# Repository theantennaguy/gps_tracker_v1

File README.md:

# gps_tracker_v1
 
This project is discontinued. I'm working on a new version, but so far it's only in the design phase.

The hardware project for this project is complete and functional. A board-bring-up was sucessfully performed and all is operational. The code was never completed, only basic functions for capturing GPS coordinates and sending SMSs, but I never got ot finish a working application for it.

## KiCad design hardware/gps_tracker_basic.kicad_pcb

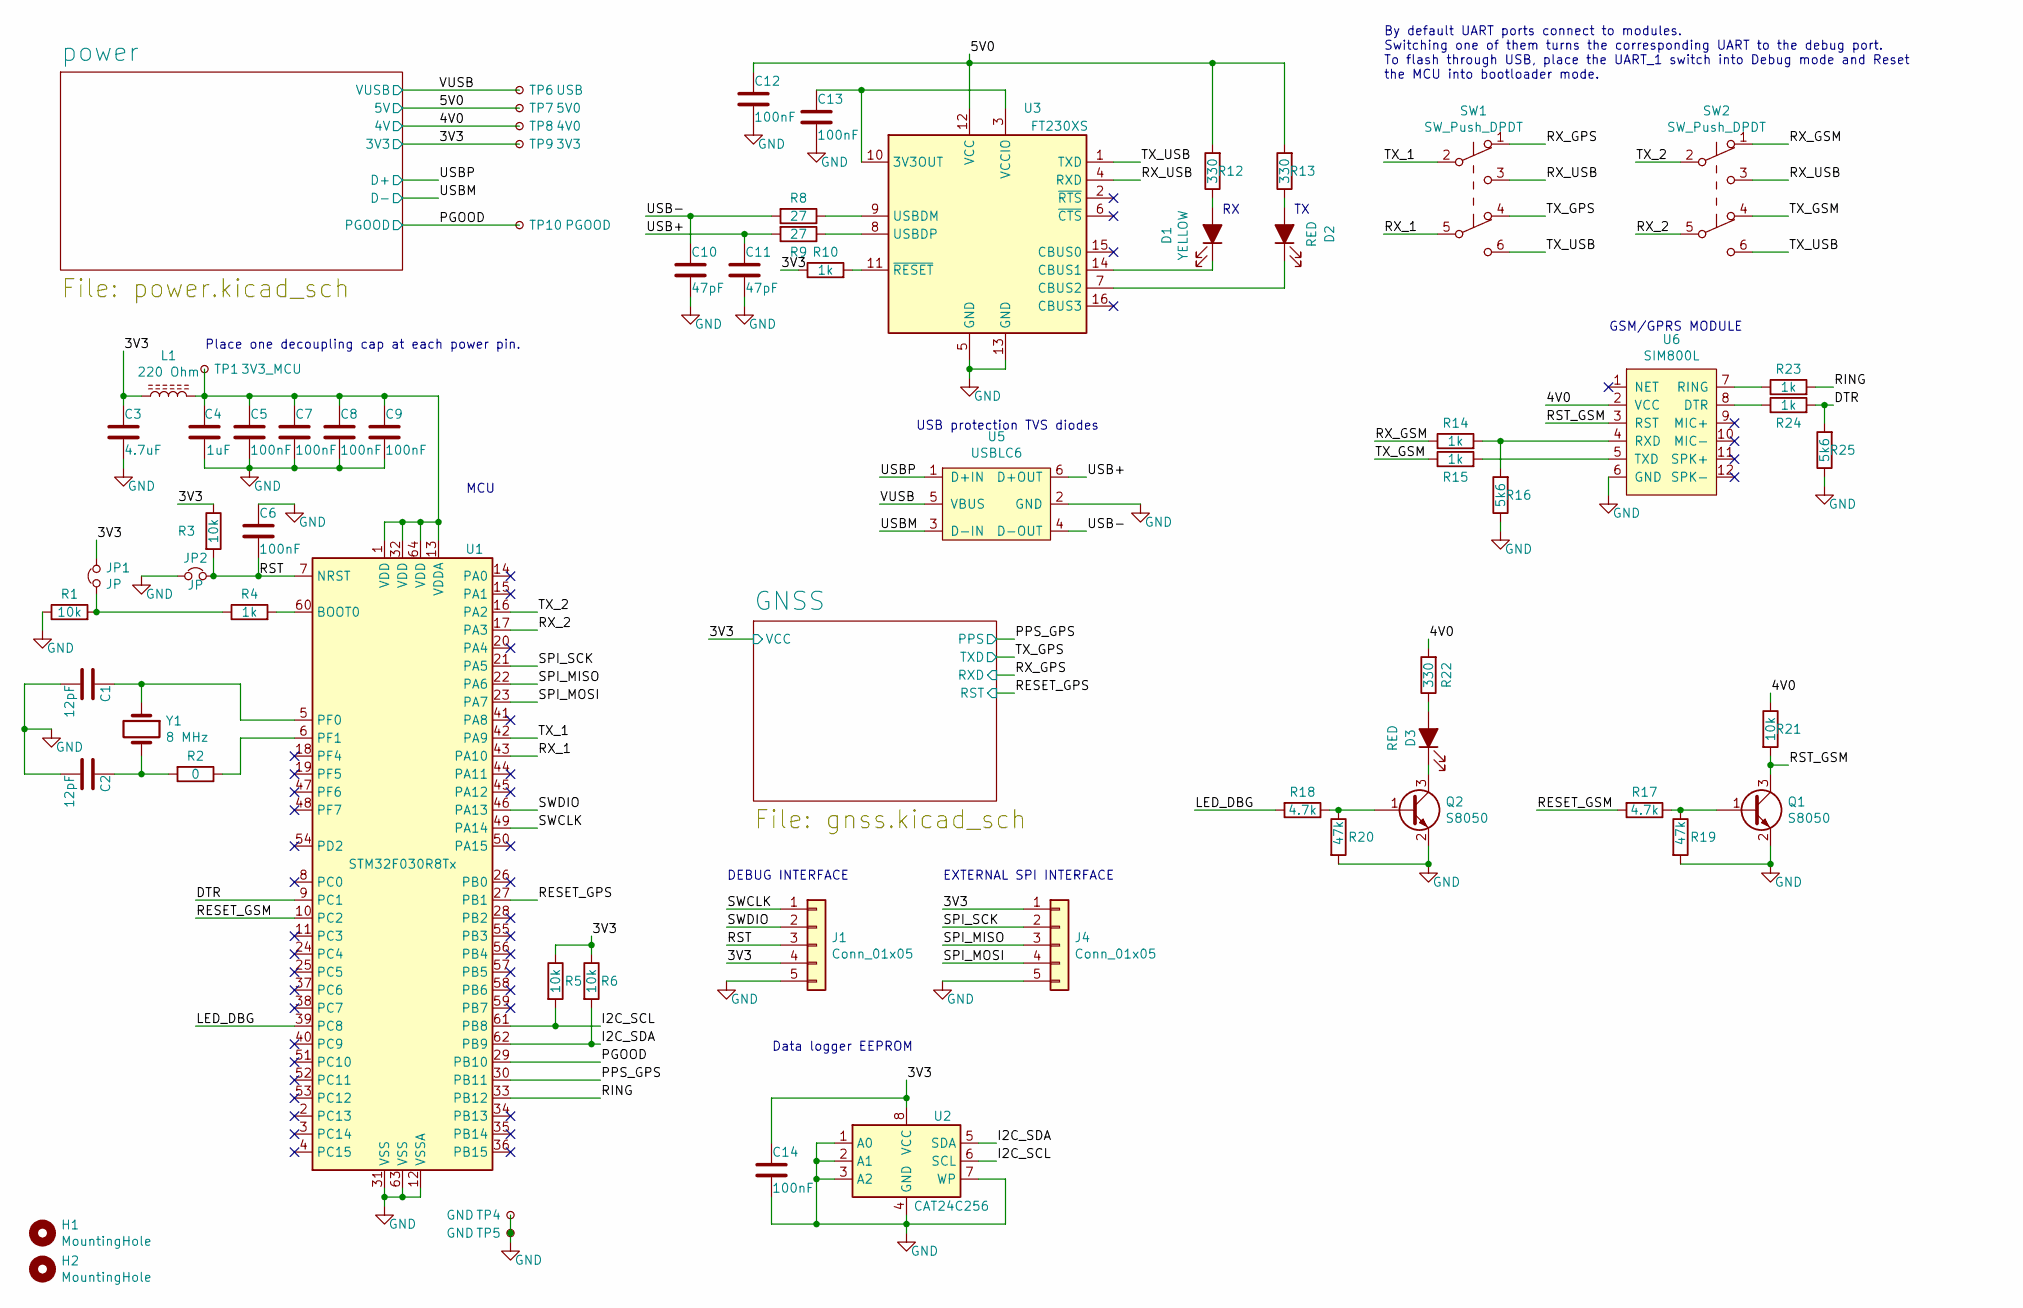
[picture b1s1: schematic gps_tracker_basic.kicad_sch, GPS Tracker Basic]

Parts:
C1, C2: 12pF; C_0402_1005Metric; Mfr. PN 0402CG120J500NT; LCSC C1547
C3: 4.7uF; C_0603_1608Metric; Mfr. PN CL10A475KO8NNNC; LCSC C19666
C4: 1uF; C_0603_1608Metric; Mfr. PN CL10A105KB8NNNC; LCSC C15849
C5, C6, C7, C8, C9, C12, C13, C14: 100nF; C_0402_1005Metric; Mfr. PN CL05B104KO5NNNC; LCSC C1525
C10, C11: 47pF; C_0402_1005Metric; Mfr. PN 0402CG470J500NT; LCSC C1567
D1: YELLOW; LED_0805_2012Metric; Mfr. PN 17-21SUYC/TR8; LCSC C2296
D2, D3: RED; LED_0805_2012Metric; Mfr. PN FC-2012HRK-620D; LCSC C84256
H1, H2: MountingHole; MountingHole_2.5mm
J1, J4: Conn_01x05; PinHeader_1x05_P2.54mm_Horizontal
JP1, JP2: JP; SolderJumper-2_P1.3mm_Open_RoundedPad1.0x1.5mm
L1: 220 Ohm; L_0603_1608Metric; Mfr. PN BLM18BB221SN1D; LCSC C85826
Q1, Q2: S8050; SOT-23; Mfr. PN S8050; LCSC C2146
R1, R3, R5, R6, R21: 10k; R_0402_1005Metric; Mfr. PN 0402WGF1002TCE; LCSC C25744
R2: 0; R_0603_1608Metric
R4, R10, R14, R15, R23, R24: 1k; R_0402_1005Metric; Mfr. PN 0402WGF1001TCE; LCSC C11702
R8, R9: 27; R_0402_1005Metric; Mfr. PN RT0402FRE0727RL
R12, R13, R22: 330; R_0402_1005Metric; Mfr. PN 0402WGF3300TCE; LCSC C25104
R16, R25: 5k6; R_0402_1005Metric; Mfr. PN 0402WGF5601TCE; LCSC C25908
R17, R18: 4.7k; R_0402_1005Metric; Mfr. PN 0402WGF4701TCE; LCSC C25900
R19, R20: 47k; R_0402_1005Metric; Mfr. PN 0402WGF4702TCE; LCSC C25792
SW1, SW2: SW_Push_DPDT; SW_CuK_JS202011CQN_DPDT_Straight; Mfr. PN JS202011JCQN
TP1: 3V3_MCU; TestPoint_Pad_D1.5mm
TP4, TP5: GND; TestPoint_Pad_D1.5mm
TP6: USB; TestPoint_Pad_D1.5mm
TP7: 5V0; TestPoint_Pad_D1.5mm
TP8: 4V0; TestPoint_Pad_D1.5mm
TP9: 3V3; TestPoint_Pad_D1.5mm
TP10: PGOOD; TestPoint_Pad_D1.5mm
U1: STM32F030R8Tx; LQFP-64_10x10mm_P0.5mm; Mfr. PN STM32F030R8T6; LCSC C39105
U2: CAT24C256; SOIC-8_3.9x4.9mm_P1.27mm; Mfr. PN AT24C256C-SSHL-T; LCSC C6482
U3: FT230XS; SSOP-16_3.9x4.9mm_P0.635mm; Mfr. PN FT230XS
U5: USBLC6; SOT-23-6; Mfr. PN USBLC6-2SC6; LCSC C7519
U6: SIM800L; SIM_800L_breakout; Mfr. PN SIM800L
Y1: 8 MHz; Crystal_SMD_5032-2Pin_5.0x3.2mm; Mfr. PN ECS-80-12-30Q-DS-TR

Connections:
/3V3: C3.1, C14.1, J1.4, J4.1, JP1.2, L1.1, R3.1, R5.1, R6.1, R10.1, TP9.1, U2.8 (VCC); also elsewhere on the board
/4V0: R21.1, R22.2, TP8.1, U6.2 (VCC); also elsewhere on the board
/5V0: C12.1, R12.2, R13.2, TP7.1, U3.12 (VCC); also elsewhere on the board
/DTR: R24.2, R25.2, U1.9 (PC1)
/I2C_SCL: R5.2, U1.61 (PB8), U2.6 (SCL)
/I2C_SDA: R6.2, U1.62 (PB9), U2.5 (SDA)
/LED_DBG: R18.2, U1.39 (PC8)
/PGOOD: TP10.1, U1.29 (PB10); also elsewhere on the board
/PPS_GPS: U1.30 (PB11); also elsewhere on the board
/RESET_GPS: U1.27 (PB1); also elsewhere on the board
/RESET_GSM: R17.2, U1.10 (PC2)
/RING: R23.2, U1.33 (PB12)
/RST: C6.2, J1.3, JP2.2, R3.2, U1.7 (NRST); also elsewhere on the board
/RST_GSM: Q1.3 (C), R21.2, U6.3 (RST)
/RX_1: SW1.5 (B), U1.43 (PA10)
/RX_2: SW2.5 (B), U1.17 (PA3)
/RX_GPS: SW1.1 (A); also elsewhere on the board
/RX_GSM: R14.1, SW2.1 (A)
/RX_USB: SW1.3 (C), SW2.3 (C), U3.4 (RXD)
/SPI_MISO: J4.3, U1.22 (PA6)
/SPI_MOSI: J4.4, U1.23 (PA7)
/SPI_SCK: J4.2, U1.21 (PA5)
/SWCLK: J1.1, U1.49 (PA14)
/SWDIO: J1.2, U1.46 (PA13)
/TX_1: SW1.2 (B), U1.42 (PA9)
/TX_2: SW2.2 (B), U1.16 (PA2)
/TX_GPS: SW1.4 (A); also elsewhere on the board
/TX_GSM: R15.1, SW2.4 (A)
/TX_USB: SW1.6 (C), SW2.6 (C), U3.1 (TXD)
/USB+: C11.1, R9.2, U5.6 (D+OUT)
/USB-: C10.1, R8.2, U5.4 (D-OUT)
/USBM: U5.3 (D-IN); also elsewhere on the board
/USBP: U5.1 (D+IN); also elsewhere on the board
/VUSB: TP6.1, U5.5 (VBUS); also elsewhere on the board
GND: C1.2, C2.2, C3.2, C4.2, C5.2, C6.1, C7.2, C8.2, C9.2, C10.2, C11.2, C12.2, C13.2, C14.2, J1.5, J4.5, JP2.1, Q1.2 (E), Q2.2 (E), R1.1, R16.1, R19.2, R20.2, R25.1, TP4.1, TP5.1, U1.12 (VSSA), U1.31 (VSS), U1.63 (VSS), U2.1 (A0), U2.2 (A1), U2.3 (A2), U2.4 (GND), U2.7 (WP), U3.5 (GND), U3.13 (GND), U5.2 (GND), U6.6 (GND); also elsewhere on the board
unnamed: C1.1, U1.5 (PF0), Y1.1
unnamed: C2.1, R2.2, Y1.2
unnamed: C4.1, C5.1, C7.1, C8.1, C9.1, L1.2, TP1.1, U1.1 (VDD), U1.13 (VDDA), U1.32 (VDD), U1.64 (VDD)
unnamed: C13.1, U3.3 (VCCIO), U3.10 (3V3OUT)
unnamed: D1.1 (K), U3.14 (CBUS1)
unnamed: D1.2 (A), R12.1
unnamed: D2.1 (K), U3.7 (CBUS2)
unnamed: D2.2 (A), R13.1
unnamed: D3.1 (K), Q2.3 (C)
unnamed: D3.2 (A), R22.1
unnamed 51: JP1.1, R1.2, R4.1; also elsewhere on the board
unnamed: Q1.1 (B), R17.1, R19.1
unnamed: Q2.1 (B), R18.1, R20.1
unnamed: R2.1, U1.6 (PF1)
unnamed: R4.2, U1.60 (BOOT0)
unnamed: R8.1, U3.9 (USBDM)
unnamed: R9.1, U3.8 (USBDP)
unnamed: R10.2, U3.11 (~RESET)
unnamed: R14.2, R16.2, U6.4 (RXD)
unnamed: R15.2, U6.5 (TXD)
unnamed: R23.1, U6.7 (RING)
unnamed: R24.1, U6.8 (DTR)

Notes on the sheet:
Place one decoupling cap at each power pin.
By default UART ports connect to modules. Switching one of them turns the corresponding UART to the debug port. To flash through USB, place the UART_1 switch into Debug mode and Reset the MCU into bootloader mode.
DEBUG INTERFACE
USB protection TVS diodes
EXTERNAL SPI INTERFACE
MCU
Data logger EEPROM
GSM/GPRS MODULE

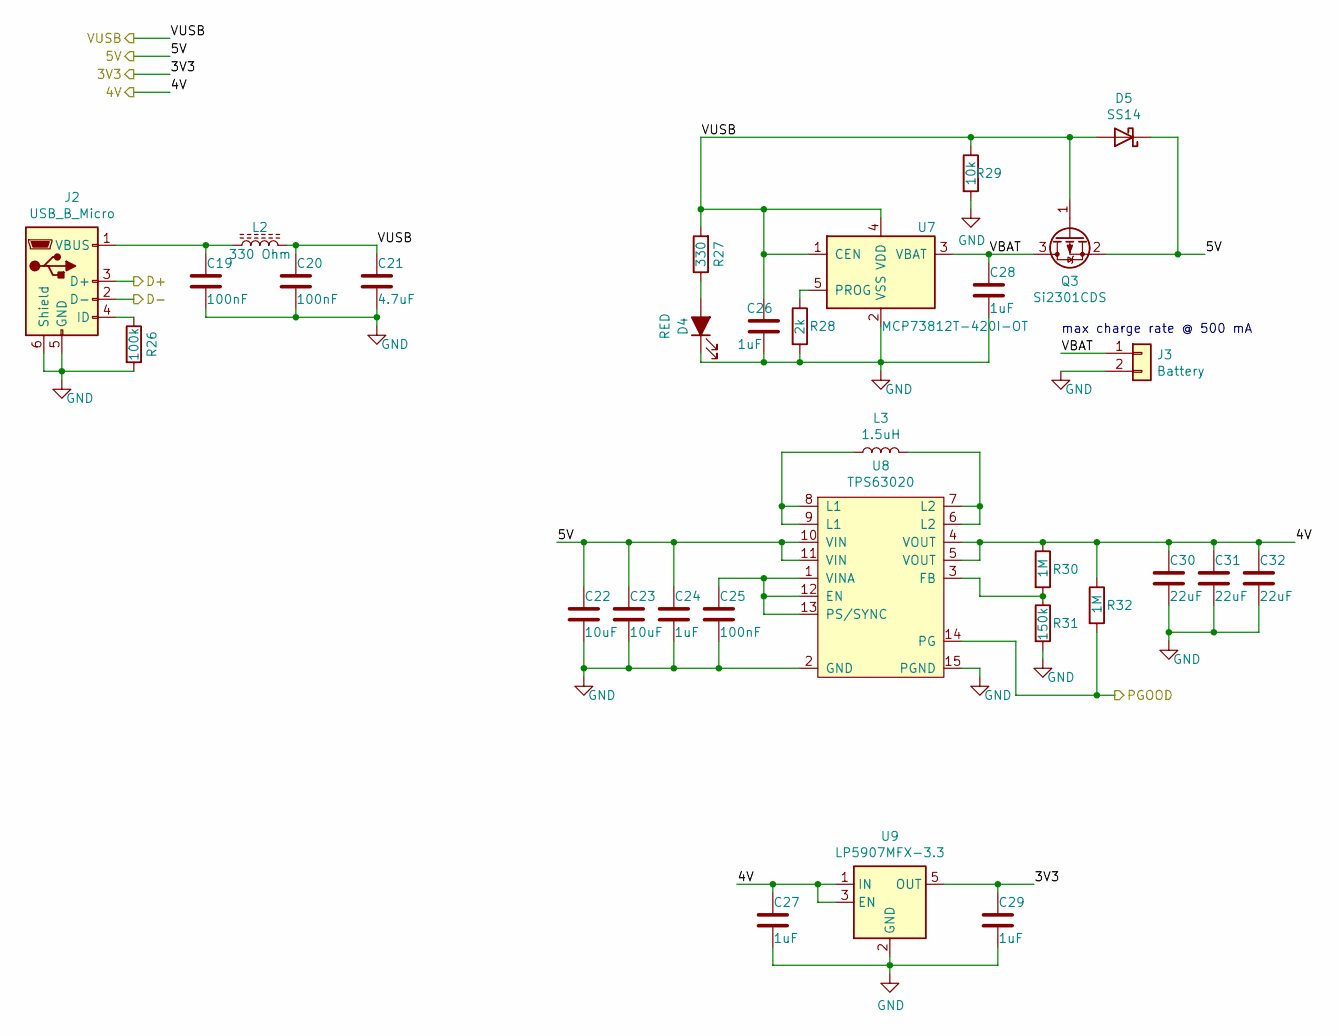
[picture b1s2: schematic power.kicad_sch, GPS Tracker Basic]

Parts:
C19, C20, C25: 100nF; C_0402_1005Metric; Mfr. PN CL05B104KO5NNNC; LCSC C1525
C21: 4.7uF; C_0603_1608Metric; Mfr. PN CL10A475KO8NNNC; LCSC C19666
C22, C23: 10uF; C_0603_1608Metric; Mfr. PN CL10A106KP8NNNC; LCSC C19702
C24, C26, C27, C28, C29: 1uF; C_0603_1608Metric; Mfr. PN CL10A105KB8NNNC; LCSC C15849
C30, C31, C32: 22uF; C_0805_2012Metric; Mfr. PN CL21A226MAQNNNE; LCSC C45783
D4: RED; LED_0805_2012Metric; Mfr. PN FC-2012HRK-620D; LCSC C84256
D5: SS14; D_SMA; Mfr. PN SS14; LCSC C2480
J2: USB_B_Micro; USB_Micro-B_Amphenol_10118194_Horizontal; Mfr. PN 10118194-0001LF
J3: Battery; PinHeader_1x02_P2.00mm_Vertical
L2: 330 Ohm; L_0805_2012Metric; Mfr. PN BLM21PG331SN1D
L3: 1.5uH; L_Bourns_SRN6045TA; Mfr. PN SRN6045TA-1R5Y
Q3: Si2301CDS; SOT-23; Mfr. PN SI2301CDS-T1-GE3; LCSC C10487
R26: 100k; R_0603_1608Metric; Mfr. PN 0603WAF1003T5E; LCSC C25803
R27: 330; R_0402_1005Metric; Mfr. PN 0402WGF3300TCE; LCSC C25104
R28: 2k; R_0402_1005Metric; Mfr. PN 0402WGF2001TCE; LCSC C4109
R29: 10k; R_0402_1005Metric; Mfr. PN 0402WGF1002TCE; LCSC C25744
R30, R32: 1M; R_0603_1608Metric; Mfr. PN 0603WAF1004T5E; LCSC C22935
R31: 150k; R_0603_1608Metric; Mfr. PN 0603WAF1503T5E; LCSC C22807
U7: MCP73812T-420I-OT; SOT-23-5; Mfr. PN MCP73812T-420I/OT; LCSC C144308
U8: TPS63020; QFN14_P0.5_4.15x3.15_wThermalVias; Mfr. PN TPS63020DSJR; LCSC C15483
U9: LP5907MFX-3.3; SOT-23-5; Mfr. PN LP5907MFX-3.3/NOPB; LCSC C80670

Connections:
/3V3: C29.1, U9.5 (OUT); also elsewhere on the board
/4V0: C27.1, C30.1, C31.1, C32.1, R30.1, R32.1, U8.4 (VOUT), U8.5 (VOUT), U9.1 (IN), U9.3 (EN); also elsewhere on the board
/5V0: C22.1, C23.1, C24.1, D5.1 (K), Q3.2 (S), U8.10 (VIN), U8.11 (VIN); also elsewhere on the board
/PGOOD: R32.2, U8.14 (PG); also elsewhere on the board
/USBM: J2.2 (D-); also elsewhere on the board
/USBP: J2.3 (D+); also elsewhere on the board
/VUSB: C20.1, C21.1, C26.1, D5.2 (A), L2.2, Q3.1 (G), R27.2, R29.1, U7.1 (CEN), U7.4 (VDD); also elsewhere on the board
/power/VBAT: C28.1, J3.1, Q3.3 (D), U7.3 (VBAT)
GND: C19.2, C20.2, C21.2, C22.2, C23.2, C24.2, C25.2, C26.2, C27.2, C28.2, C29.2, C30.2, C31.2, C32.2, D4.1 (K), J2.5 (GND), J2.6 (Shield), J3.2, R26.2, R28.2, R29.2, R31.2, U7.2 (VSS), U8.2 (GND), U8.15 (PGND), U9.2 (GND); also elsewhere on the board
unnamed: C19.1, J2.1 (VBUS), L2.1
unnamed: C25.1, U8.1 (VINA), U8.12 (EN), U8.13 (PS/SYNC)
unnamed: D4.2 (A), R27.1
unnamed: J2.4 (ID), R26.1
unnamed: L3.1, U8.8 (L1), U8.9 (L1)
unnamed: L3.2, U8.6 (L2), U8.7 (L2)
unnamed: R28.1, U7.5 (PROG)
unnamed: R30.2, R31.1, U8.3 (FB)

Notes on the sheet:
max charge rate @ 500 mA

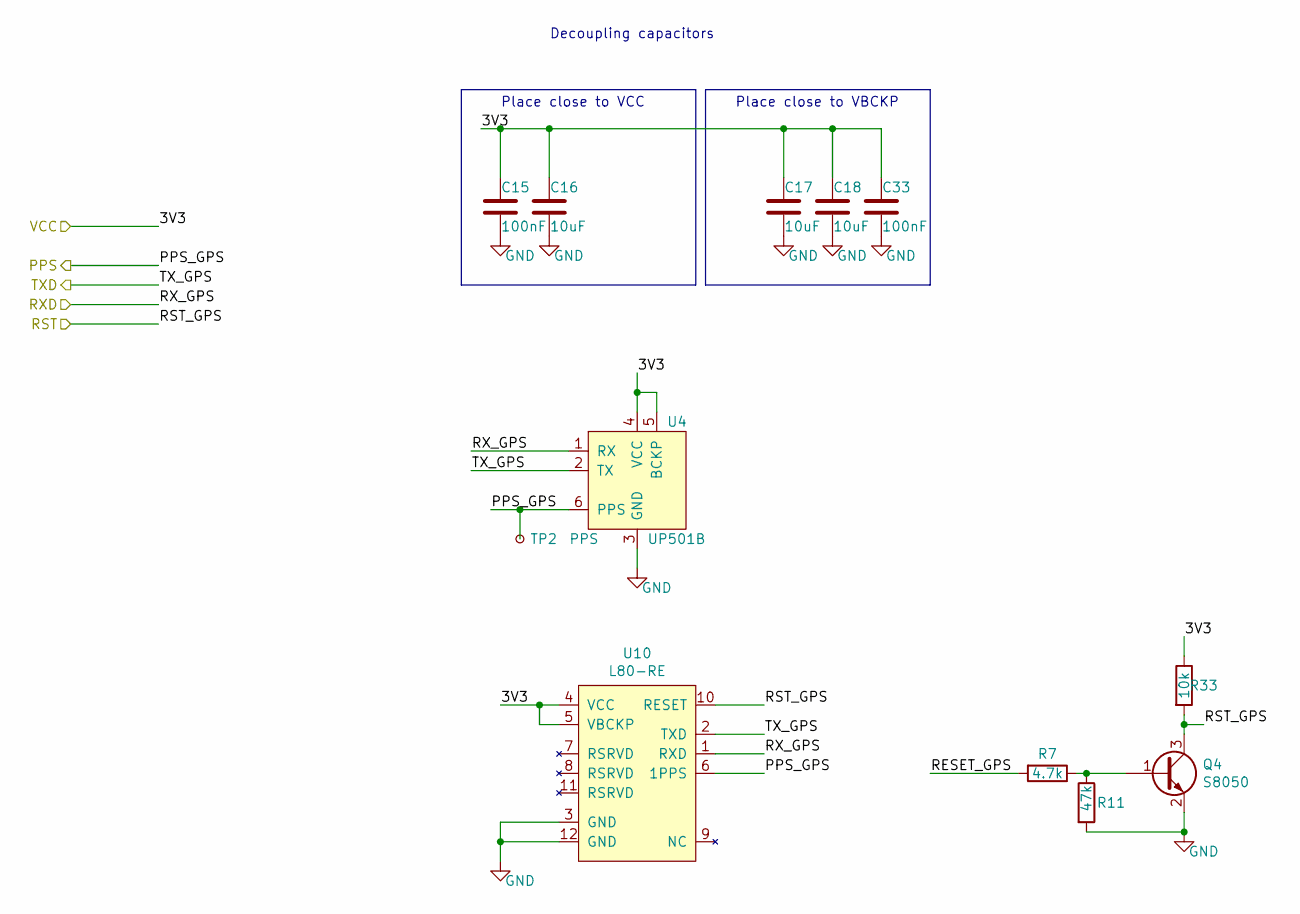
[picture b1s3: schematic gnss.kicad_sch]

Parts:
C15, C33: 100nF; C_0402_1005Metric; Mfr. PN CL05B104KO5NNNC; LCSC C1525
C16, C17, C18: 10uF; C_0603_1608Metric; Mfr. PN CL10A106KP8NNNC; LCSC C19702
Q4: S8050; SOT-23; Mfr. PN S8050; LCSC C2146
R7: 4.7k; R_0402_1005Metric; Mfr. PN 0402WGF4701TCE; LCSC C25900
R11: 47k; R_0402_1005Metric; Mfr. PN 0402WGF4702TCE; LCSC C25792
R33: 10k; R_0402_1005Metric; Mfr. PN 0402WGF1002TCE; LCSC C25744
TP2: PPS; TestPoint_Pad_D1.5mm
U4: UP501B; Mfr. PN UP501B
U10: L80-RE; L80RE; Mfr. PN L80RE-M37

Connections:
/3V3: C15.1, C16.1, C17.1, C18.1, C33.1, R33.1, U4.4 (VCC), U4.5 (BCKP), U10.4 (VCC), U10.5 (VBCKP); also elsewhere on the board
/GNSS/RESET_GPS: R7.2
/PPS_GPS: TP2.1, U4.6 (PPS), U10.6 (1PPS); also elsewhere on the board
/RESET_GPS: Q4.3 (C), R33.2, U10.10 (RESET); also elsewhere on the board
/RX_GPS: U4.1 (RX), U10.1 (RXD); also elsewhere on the board
/TX_GPS: U4.2 (TX), U10.2 (TXD); also elsewhere on the board
GND: C15.2, C16.2, C17.2, C18.2, C33.2, Q4.2 (E), R11.2, U4.3 (GND), U10.3 (GND), U10.12 (GND); also elsewhere on the board
unnamed: Q4.1 (B), R7.1, R11.1

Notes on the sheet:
Place close to VBCKP
Place close to VCC
Decoupling capacitors

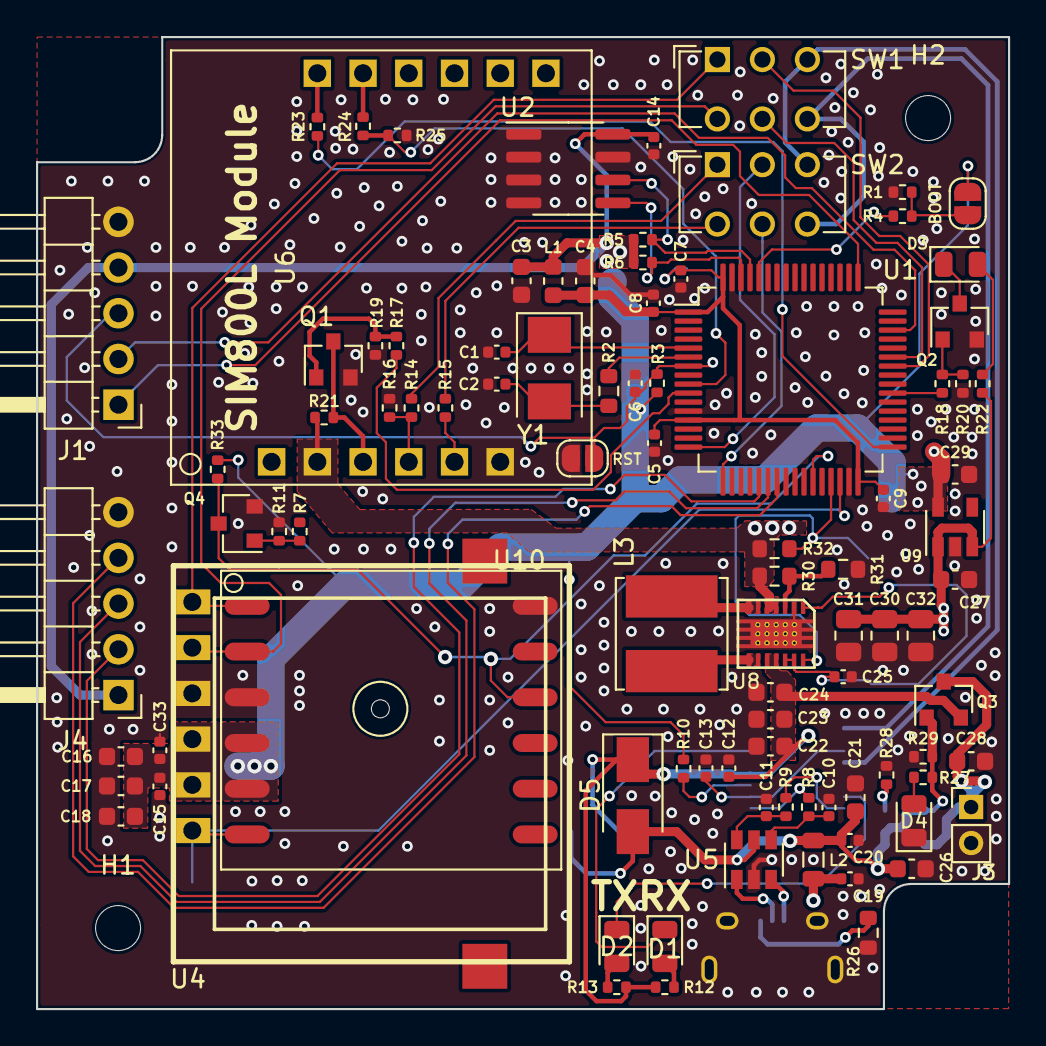
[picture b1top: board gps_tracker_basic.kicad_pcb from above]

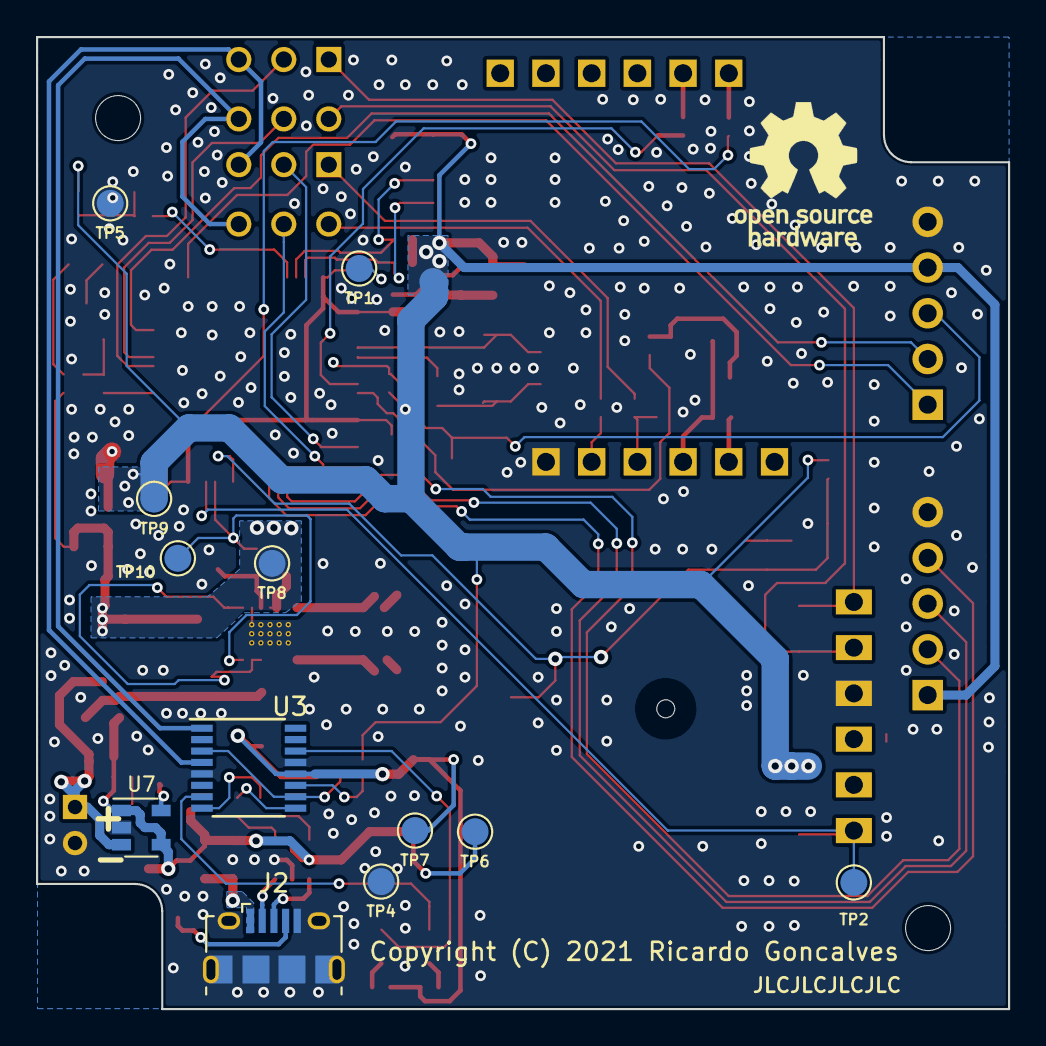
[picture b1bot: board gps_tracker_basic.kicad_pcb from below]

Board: 2 copper layers, 54.0 x 54.0 mm, 108 parts (12 on the bottom side), 67 nets.

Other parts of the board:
BOOT: JP; SolderJumper-2_P1.3mm_Open_RoundedPad1.0x1.5mm
RST: JP; SolderJumper-2_P1.3mm_Open_RoundedPad1.0x1.5mm

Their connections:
/3V3: BOOT.2; also elsewhere on the board
/RST: RST.2; also elsewhere on the board
GND: RST.1; also elsewhere on the board
unnamed 51: BOOT.1; also elsewhere on the board

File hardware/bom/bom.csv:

Reference, Quantity, Value, Footprint, LCSC, Manufacturer, Mfr. PN, Supplier, Supplier PN
C1 C2 ,2,12pF,Capacitor_SMD:C_0402_1005Metric,C1547,Guangdong Fenghua Advanced Tech,0402CG120J500NT,LCSC,C1547
C10 C11 ,2,47pF,Capacitor_SMD:C_0402_1005Metric,C1567,Guangdong Fenghua Advanced Tech,0402CG470J500NT,LCSC,C1567
C5 C6 C7 C8 C9 C12 C13 C14 C15 C19 C20 C25 C33 ,13,100nF,Capacitor_SMD:C_0402_1005Metric,C1525,Samsung Electro-Mechanics,CL05B104KO5NNNC,LCSC,C1525
C16 C17 C18 C22 C23 ,5,10uF,Capacitor_SMD:C_0603_1608Metric,C19702,Samsung Electro-Mechanics,CL10A106KP8NNNC,LCSC,C19702
C3 C21 ,2,4.7uF,Capacitor_SMD:C_0603_1608Metric,C19666,SAMSUNG,CL10A475KO8NNNC,LCSC,C19666
C30 C31 C32 ,3,22uF,Resistor_SMD:R_0805_2012Metric,C45783,Samsung Electro-Mechanics,CL21A226MAQNNNE,LCSC,C45783
C4 C24 C26 C27 C28 C29 ,6,1uF,Capacitor_SMD:C_0603_1608Metric,C15849,Samsung Electro-Mechanics,CL10A105KB8NNNC,LCSC,C15849
D1 ,1,YELLOW,LED_SMD:LED_0805_2012Metric,C2296,Hubei KENTO Elec,17-21SUYC/TR8,LCSC,C2296
D2 D3 D4 ,3,RED,LED_SMD:LED_0805_2012Metric,C84256,Foshan NationStar Optoelectronics,FC-2012HRK-620D,LCSC,C84256
D5 ,1,SS14,Diode_SMD:D_SMA,C2480,MDD( Microdiode Electronics),SS14,LCSC,C2480
Q1 Q2 Q4 ,3,S8050,Package_TO_SOT_SMD:SOT-23,C2146,Changjiang Electronics Tech (CJ),S8050,LCSC,C2146
Q3 ,1,Si2301CDS,Package_TO_SOT_SMD:SOT-23,C10487,Vishay Intertech,SI2301CDS-T1-GE3,LCSC,C10487
R12 R13 R22 R27 ,4,330,Resistor_SMD:R_0402_1005Metric,C25104,Uniroyal Elec,0402WGF3300TCE,LCSC,C25104
R4 R10 R14 R15 R23 R24 ,6,1k,Resistor_SMD:R_0402_1005Metric,C11702,Uniroyal Elec,0402WGF1001TCE,LCSC,C11702
R16 R25 ,2,5k6,Resistor_SMD:R_0402_1005Metric,C25908,Uniroyal Elec,0402WGF5601TCE,LCSC,C25908
R7 R17 R18 ,3,4.7k,Resistor_SMD:R_0402_1005Metric,C25900,Uniroyal Elec,0402WGF4701TCE,LCSC,C25900
R11 R19 R20 ,3,47k,Resistor_SMD:R_0402_1005Metric,C25792,Uniroyal Elec,0402WGF4702TCE,LCSC,C25792
R1 R3 R5 R6 R21 R29 R33 ,7,10k,Resistor_SMD:R_0402_1005Metric,C25744,Uniroyal Elec,0402WGF1002TCE,LCSC,C25744
R26 ,1,100k,Resistor_SMD:R_0603_1608Metric,C25803,Uniroyal Elec,0603WAF1003T5E,LCSC,C25803
R28 ,1,2k,Resistor_SMD:R_0402_1005Metric,C4109,Uniroyal Elec,0402WGF2001TCE,LCSC,C4109
R31 ,1,150k,Resistor_SMD:R_0603_1608Metric,C22807,Uniroyal Elec,0603WAF1503T5E,LCSC,C22807
R30 R32 ,2,1M,Resistor_SMD:R_0603_1608Metric,C22935,Uniroyal Elec,0603WAF1004T5E,LCSC,C22935
U2 ,1,CAT24C256,Package_SO:SOIC-8_3.9x4.9mm_P1.27mm,C6482,Microchip Tech,AT24C256C-SSHL-T,LCSC,C6482
U8 ,1,TPS63020,gps_tracker:QFN14_P0.5_4.15x3.15_wThermalVias,C15483,Texas Instruments,TPS63020DSJR,LCSC,C15483

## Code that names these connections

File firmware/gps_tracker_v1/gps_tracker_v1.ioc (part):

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PA6.Mode=Full_Duplex_Master
PA7.Mode=Full_Duplex_Master
PA10.Mode=Asynchronous
Mcu.UserName=STM32F030R8Tx
PA9.GPIO_Label=TX_1
PC8.Signal=GPIO_Output
PA9.GPIOParameters=GPIO_Label
PC2.Signal=GPIO_Output
PB11.GPIO_Label=PPS_GPS
PA3.GPIOParameters=GPIO_Label
PB11.Signal=GPIO_Input
PA2.GPIOParameters=GPIO_Label
RCC.SYSCLKSource=RCC_SYSCLKSOURCE_PLLCLK
PC8.GPIO_Label=LED_DBG
PA3.Mode=Asynchronous
PA13.Signal=SYS_SWDIO
PA9.Mode=Asynchronous
PB10.GPIO_Label=PGOOD
PC1.GPIOParameters=GPIO_Label
PB9.Mode=I2C
PA9.Signal=USART1_TX
PB11.GPIOParameters=GPIO_Label
PF0-OSC_IN.Mode=HSE-External-Oscillator
PB10.Signal=GPIO_Input
PA5.Signal=SPI1_SCK
board=custom
PB12.GPIO_Label=RING
PA14.Mode=Serial_Wire
PC2.GPIOParameters=GPIO_Label
PB1.GPIO_Label=RESET_GPS
PC1.GPIO_Label=DTR
PA10.GPIO_Label=RX_1
PA10.GPIOParameters=GPIO_Label
PA13.Mode=Serial_Wire
Mcu.Name=STM32F030R8Tx
PA2.Signal=USART2_TX
PC8.GPIOParameters=GPIO_Label
RCC.SYSCLKFreq_VALUE=48000000
Mcu.Package=LQFP64
PB9.Signal=I2C1_SDA
PA6.Signal=SPI1_MISO
PB1.Signal=GPIO_Output
PA2.GPIO_Label=TX_2
PA10.Signal=USART1_RX
PA14.Signal=SYS_SWCLK
PB8.Mode=I2C
PA2.Mode=Asynchronous
PB8.Signal=I2C1_SCL
PB10.GPIOParameters=GPIO_Label
PF0-OSC_IN.Signal=RCC_OSC_IN
PF1-OSC_OUT.Mode=HSE-External-Oscillator
PC2.GPIO_Label=RESET_GSM
PC1.Signal=GPIO_Output
PB12.GPIOParameters=GPIO_Label
PF1-OSC_OUT.Signal=RCC_OSC_OUT
PB12.Signal=GPIO_Input
PA3.GPIO_Label=RX_2
PA3.Signal=USART2_RX
PB1.GPIOParameters=GPIO_Label
PA7.Signal=SPI1_MOSI
PA5.Mode=Full_Duplex_Master

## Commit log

2022-08-04 create repository
    crate repository with project initial data of project.
2022-08-04 Update kicad sheets
2022-08-05 Update firmware folder
2023-12-06 Update README.md
    Notice on discontinuation of the project.

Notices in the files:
hardware/gps_tracker_basic.kicad_pcb:
Copyright (C) 2021 Ricardo Goncalves
